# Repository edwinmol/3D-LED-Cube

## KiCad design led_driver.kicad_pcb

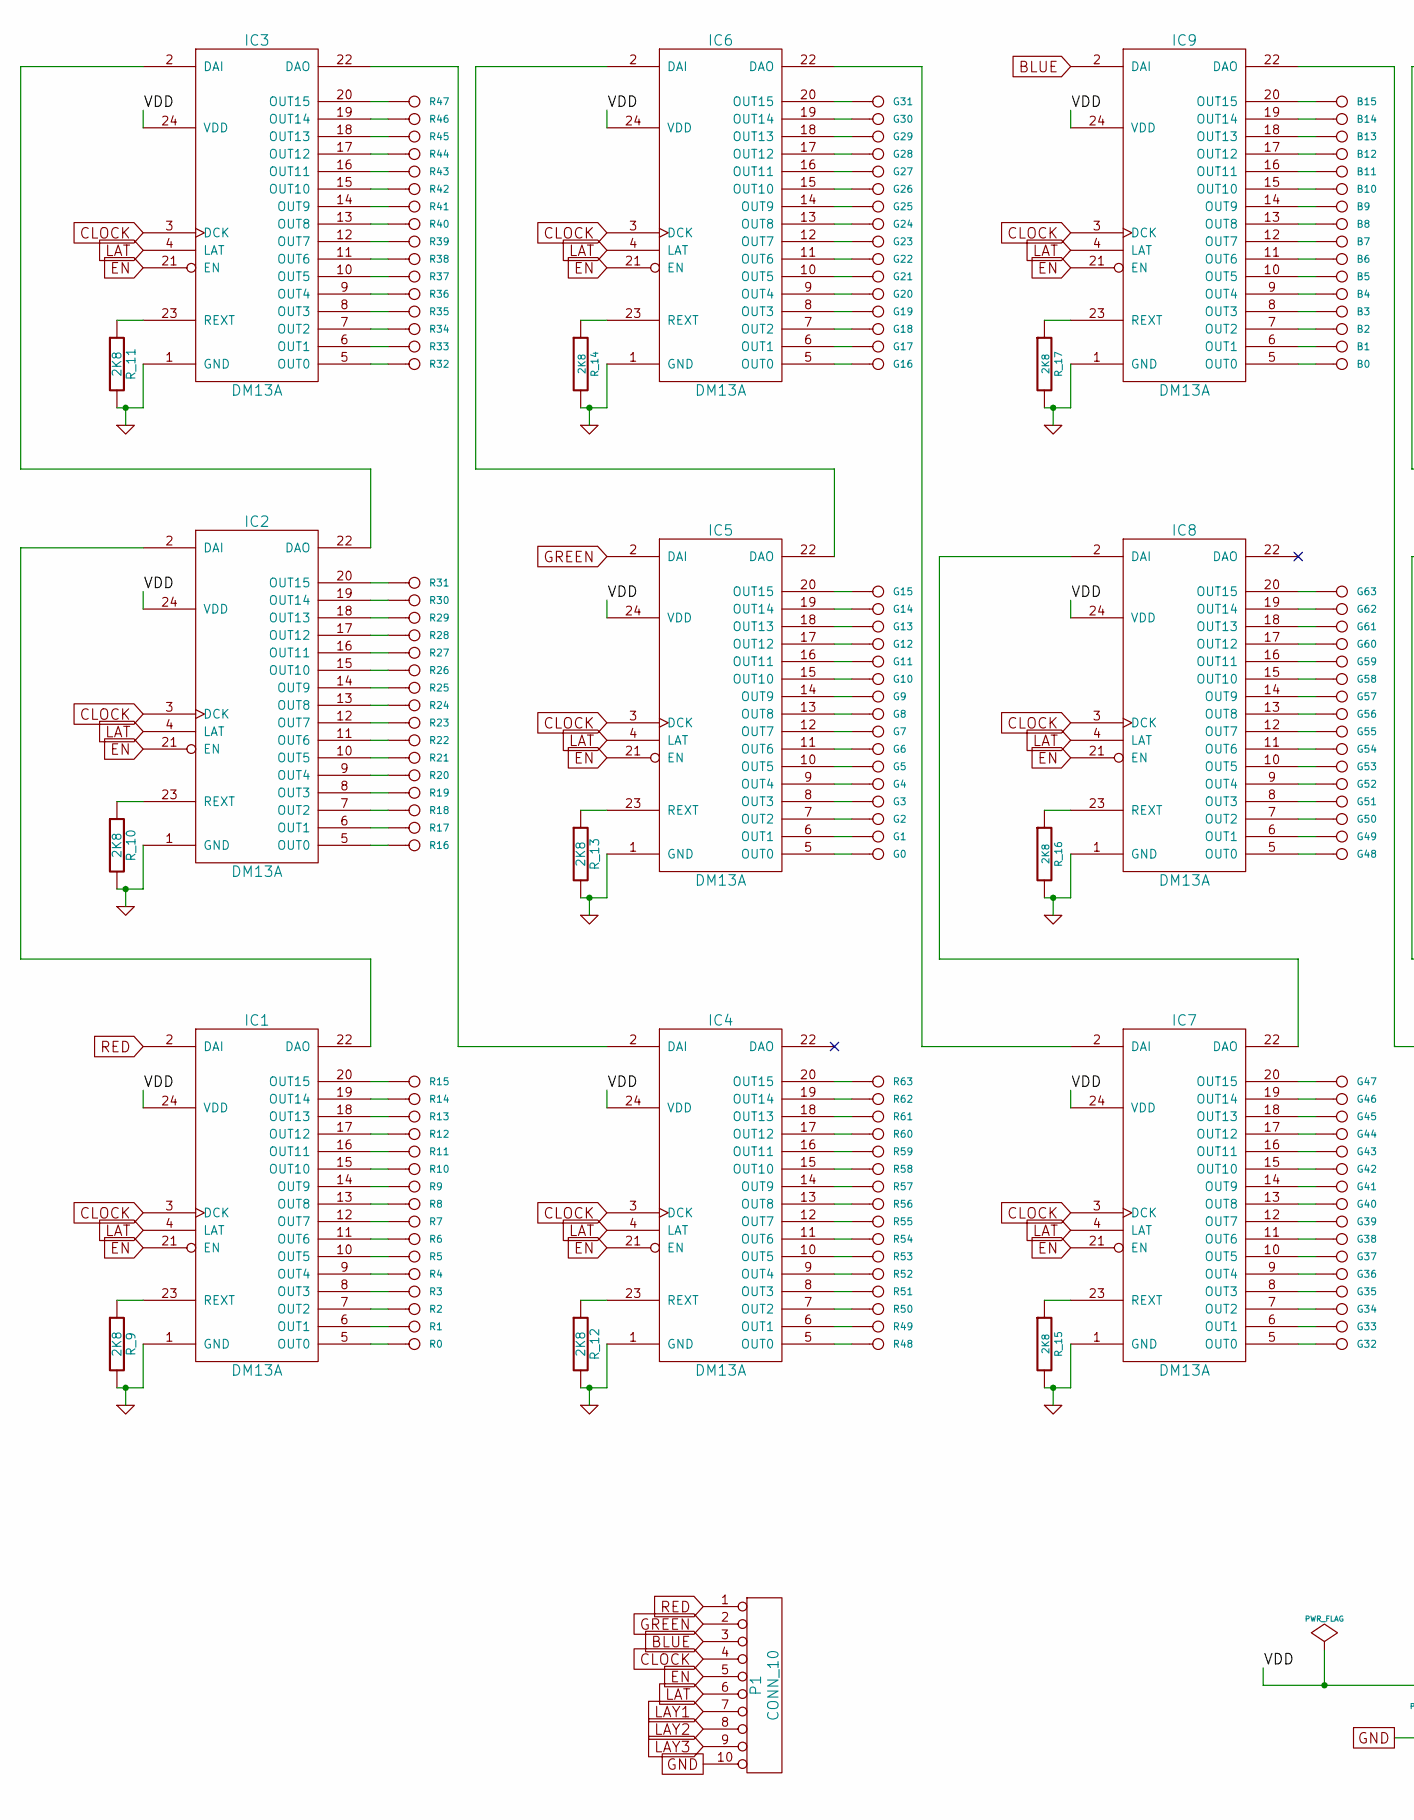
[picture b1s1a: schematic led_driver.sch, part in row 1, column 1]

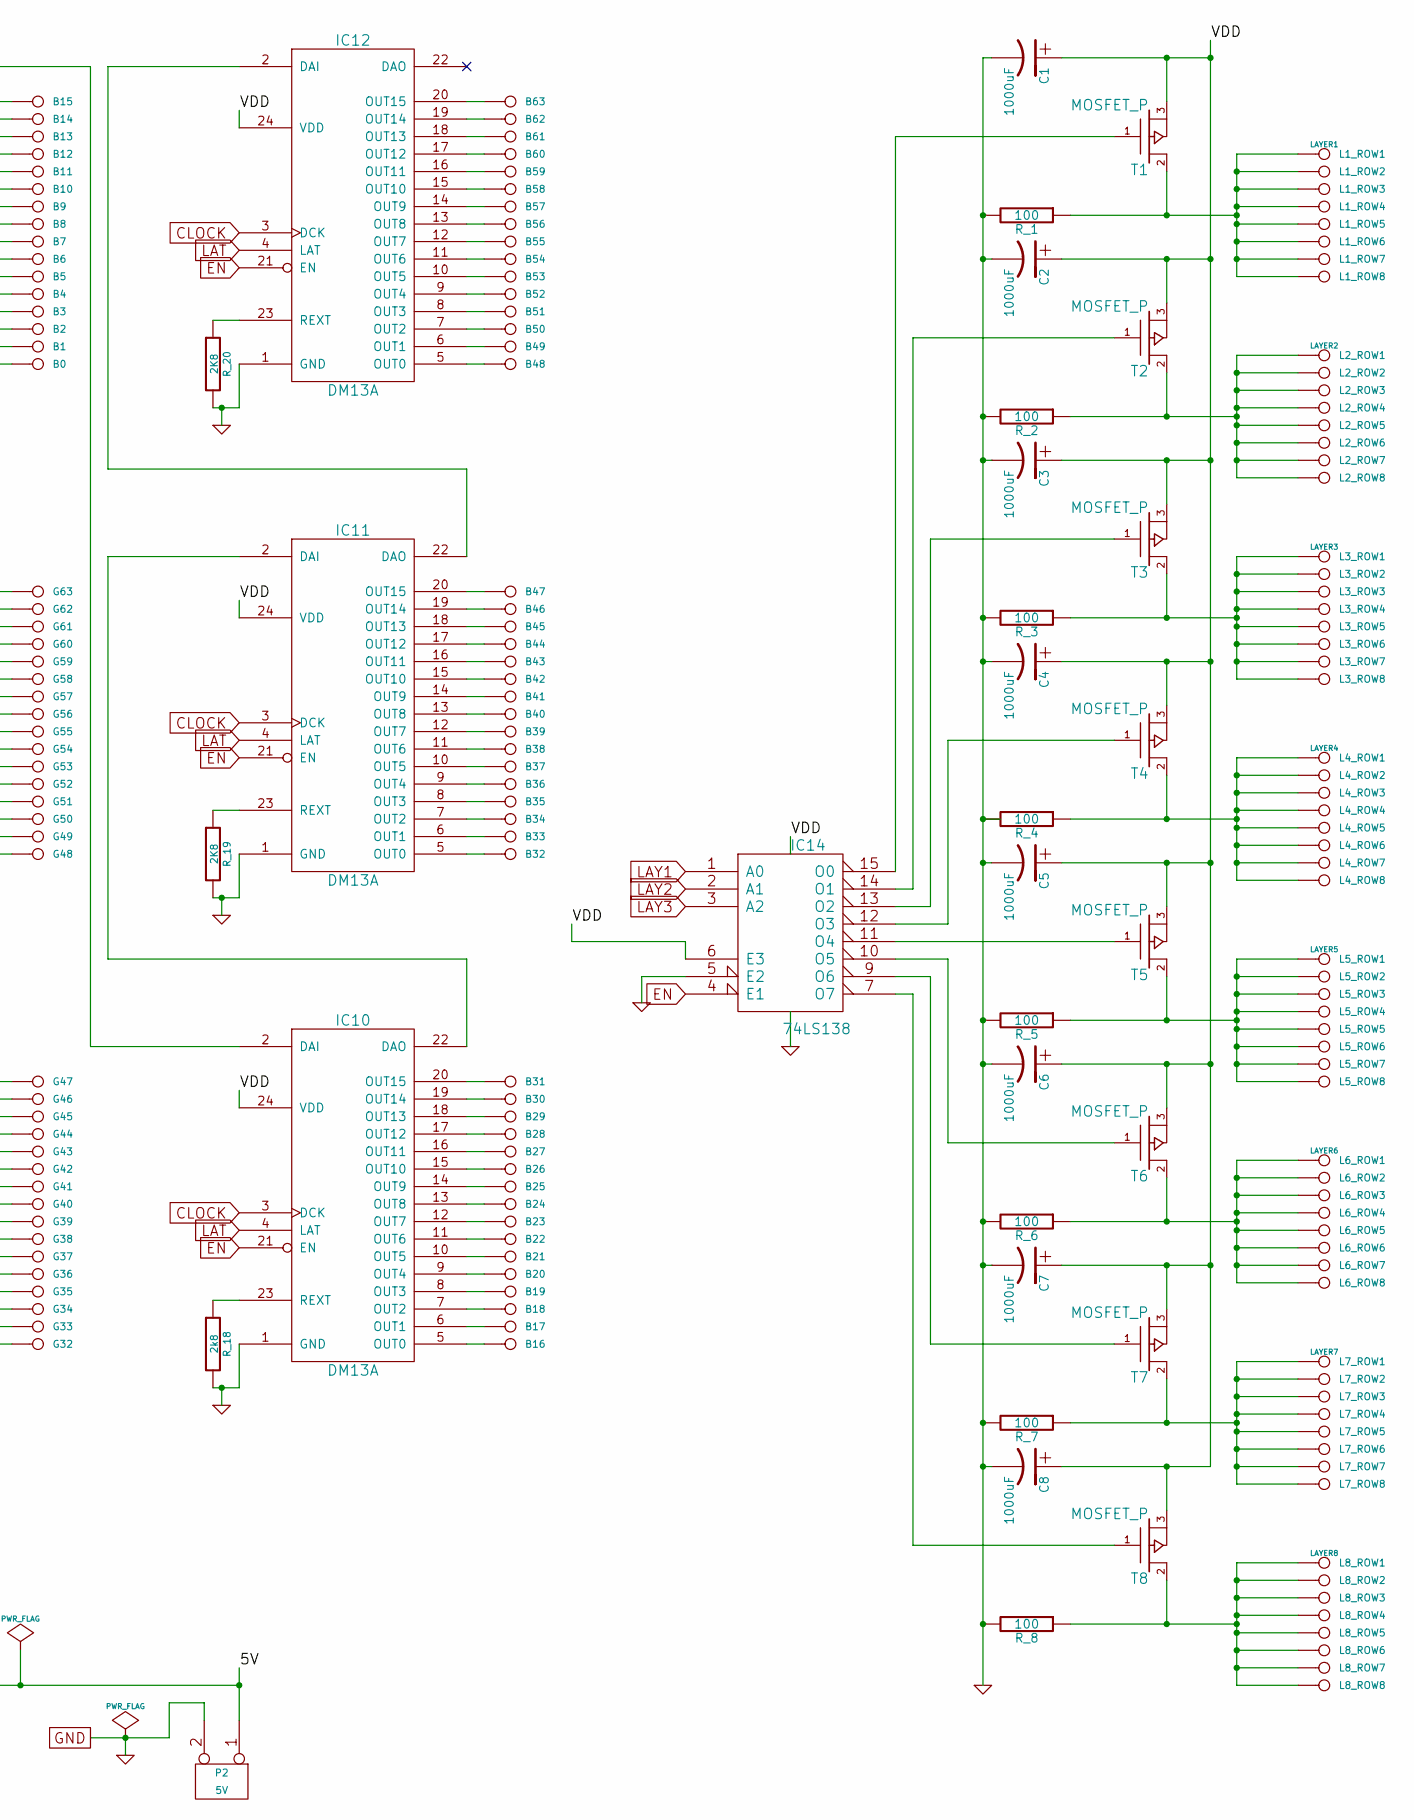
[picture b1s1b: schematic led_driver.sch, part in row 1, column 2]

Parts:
B0, B1, B2, B3, B4, B5, B6, B7, B8, B9, B10, B11, B12, B13, B14, B15, B16, B17, B18, B19, B20, B21, B22, B23, B24, B25, B26, B27, B28, B29, B30, B31, B32, B33, B34, B35, B36, B37, B38, B39, B40, B41, B42, B43, B44, B45, B46, B47, B48, B49, B50, B51, B52, B53, B54, B55, B56, B57, B58, B59, B60, B61, B62, B63: CONN_1
C1, C2, C3, C4, C5, C6, C7, C8: 1000uF
G0, G1, G2, G3, G4, G5, G6, G7, G8, G9, G10, G11, G12, G13, G14, G15, G16, G17, G18, G19, G20, G21, G22, G23, G24, G25, G26, G27, G28, G29, G30, G31, G32, G33, G34, G35, G36, G37, G38, G39, G40, G41, G42, G43, G44, G45, G46, G47, G48, G49, G50, G51, G52, G53, G54, G55, G56, G57, G58, G59, G60, G61, G62, G63: CONN_1
IC1, IC2, IC3, IC4, IC5, IC6, IC7, IC8, IC9, IC10, IC11, IC12: DM13A
IC14: 74LS138
L1_ROW1: LAYER1
L1_ROW2, L1_ROW3, L1_ROW4, L1_ROW5, L1_ROW6, L1_ROW7, L1_ROW8, L2_ROW2, L2_ROW3, L2_ROW4, L2_ROW5, L2_ROW6, L2_ROW7, L2_ROW8, L3_ROW2, L3_ROW3, L3_ROW4, L3_ROW5, L3_ROW6, L3_ROW7, L3_ROW8, L4_ROW2, L4_ROW3, L4_ROW4, L4_ROW5, L4_ROW6, L4_ROW7, L4_ROW8, L5_ROW2, L5_ROW3, L5_ROW4, L5_ROW5, L5_ROW6, L5_ROW7, L5_ROW8, L6_ROW2, L6_ROW3, L6_ROW4, L6_ROW5, L6_ROW6, L6_ROW7, L6_ROW8, L7_ROW2, L7_ROW3, L7_ROW4, L7_ROW5, L7_ROW6, L7_ROW7, L7_ROW8, L8_ROW2, L8_ROW3, L8_ROW4, L8_ROW5, L8_ROW6, L8_ROW7, L8_ROW8: CONN_1
L2_ROW1: LAYER2
L3_ROW1: LAYER3
L4_ROW1: LAYER4
L5_ROW1: LAYER5
L6_ROW1: LAYER6
L7_ROW1: LAYER7
L8_ROW1: LAYER8
P1: CONN_10
P2: 5V
R0, R1, R2, R3, R4, R5, R6, R7, R8, R9, R10, R11, R12, R13, R14, R15, R16, R17, R18, R19, R20, R21, R22, R23, R24, R25, R26, R27, R28, R29, R30, R31, R32, R33, R34, R35, R36, R37, R38, R39, R40, R41, R42, R43, R44, R45, R46, R47, R48, R49, R50, R51, R52, R53, R54, R55, R56, R57, R58, R59, R60, R61, R62, R63: CONN_1
R_1, R_2, R_3, R_4, R_5, R_6, R_7, R_8: 100
R_9, R_10, R_11, R_12, R_13: 2K8
R_14, R_15, R_16, R_17, R_19, R_20: 2K8
R_18: 2k8
T1, T2, T3, T4, T5, T6, T7, T8: MOSFET_P

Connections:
BLUE: IC9.2 (DAI), P1.3
CLOCK: IC1.3 (DCK), IC2.3 (DCK), IC3.3 (DCK), IC4.3 (DCK), IC5.3 (DCK), IC6.3 (DCK), IC7.3 (DCK), IC8.3 (DCK), IC9.3 (DCK), IC10.3 (DCK), IC11.3 (DCK), IC12.3 (DCK), P1.4
EN: IC1.21 (EN), IC2.21 (EN), IC3.21 (EN), IC4.21 (EN), IC5.21 (EN), IC6.21 (EN), IC7.21 (EN), IC8.21 (EN), IC9.21 (EN), IC10.21 (EN), IC11.21 (EN), IC12.21 (EN), IC14.4 (E1), P1.5
GND: C1.2, C2.2, C3.2, C4.2, C5.2, C6.2, C7.2, C8.2, IC1.1 (GND), IC2.1 (GND), IC3.1 (GND), IC4.1 (GND), IC5.1 (GND), IC6.1 (GND), IC7.1 (GND), IC8.1 (GND), IC9.1 (GND), IC10.1 (GND), IC11.1 (GND), IC12.1 (GND), IC14.5 (E2), IC14.8 (GND), P1.10, P2.2 (PM), R_1.2, R_2.2, R_3.2, R_4.2, R_5.2, R_6.2, R_7.2, R_8.2, R_9.2, R_10.2, R_11.2, R_12.2, R_13.2, R_14.2, R_15.2, R_16.2, R_17.2, R_18.2, R_19.2, R_20.2
GREEN: IC5.2 (DAI), P1.2
LAT: IC1.4 (LAT), IC2.4 (LAT), IC3.4 (LAT), IC4.4 (LAT), IC5.4 (LAT), IC6.4 (LAT), IC7.4 (LAT), IC8.4 (LAT), IC9.4 (LAT), IC10.4 (LAT), IC11.4 (LAT), IC12.4 (LAT), P1.6
LAY1: IC14.1 (A0), P1.7
LAY2: IC14.2 (A1), P1.8
LAY3: IC14.3 (A2), P1.9
unnamed: B0.1, IC9.5 (OUT0)
unnamed: B1.1, IC9.6 (OUT1)
unnamed: B2.1, IC9.7 (OUT2)
unnamed: B3.1, IC9.8 (OUT3)
unnamed: B4.1, IC9.9 (OUT4)
unnamed: B5.1, IC9.10 (OUT5)
unnamed: B6.1, IC9.11 (OUT6)
unnamed: B7.1, IC9.12 (OUT7)
unnamed: B8.1, IC9.13 (OUT8)
unnamed: B9.1, IC9.14 (OUT9)
unnamed: B10.1, IC9.15 (OUT10)
unnamed: B11.1, IC9.16 (OUT11)
unnamed: B12.1, IC9.17 (OUT12)
unnamed: B13.1, IC9.18 (OUT13)
unnamed: B14.1, IC9.19 (OUT14)
unnamed: B15.1, IC9.20 (OUT15)
unnamed: B16.1, IC10.5 (OUT0)
unnamed: B17.1, IC10.6 (OUT1)
unnamed: B18.1, IC10.7 (OUT2)
unnamed: B19.1, IC10.8 (OUT3)
unnamed: B20.1, IC10.9 (OUT4)
unnamed: B21.1, IC10.10 (OUT5)
unnamed: B22.1, IC10.11 (OUT6)
unnamed: B23.1, IC10.12 (OUT7)
unnamed: B24.1, IC10.13 (OUT8)
unnamed: B25.1, IC10.14 (OUT9)
unnamed: B26.1, IC10.15 (OUT10)
unnamed: B27.1, IC10.16 (OUT11)
unnamed: B28.1, IC10.17 (OUT12)
unnamed: B29.1, IC10.18 (OUT13)
unnamed: B30.1, IC10.19 (OUT14)
unnamed: B31.1, IC10.20 (OUT15)
unnamed: B32.1, IC11.5 (OUT0)
unnamed: B33.1, IC11.6 (OUT1)
unnamed: B34.1, IC11.7 (OUT2)
unnamed: B35.1, IC11.8 (OUT3)
unnamed: B36.1, IC11.9 (OUT4)
unnamed: B37.1, IC11.10 (OUT5)
unnamed: B38.1, IC11.11 (OUT6)
unnamed: B39.1, IC11.12 (OUT7)
unnamed: B40.1, IC11.13 (OUT8)
unnamed: B41.1, IC11.14 (OUT9)
unnamed: B42.1, IC11.15 (OUT10)
unnamed: B43.1, IC11.16 (OUT11)
unnamed: B44.1, IC11.17 (OUT12)
unnamed: B45.1, IC11.18 (OUT13)
unnamed: B46.1, IC11.19 (OUT14)
unnamed: B47.1, IC11.20 (OUT15)
unnamed: B48.1, IC12.5 (OUT0)
unnamed: B49.1, IC12.6 (OUT1)
unnamed: B50.1, IC12.7 (OUT2)
unnamed: B51.1, IC12.8 (OUT3)
unnamed: B52.1, IC12.9 (OUT4)
unnamed: B53.1, IC12.10 (OUT5)
unnamed: B54.1, IC12.11 (OUT6)
unnamed: B55.1, IC12.12 (OUT7)
unnamed: B56.1, IC12.13 (OUT8)
unnamed: B57.1, IC12.14 (OUT9)
unnamed: B58.1, IC12.15 (OUT10)
unnamed: B59.1, IC12.16 (OUT11)
unnamed: B60.1, IC12.17 (OUT12)
unnamed: B61.1, IC12.18 (OUT13)
unnamed: B62.1, IC12.19 (OUT14)
unnamed: B63.1, IC12.20 (OUT15)
unnamed: G0.1, IC5.5 (OUT0)
unnamed: G1.1, IC5.6 (OUT1)
unnamed: G2.1, IC5.7 (OUT2)
unnamed: G3.1, IC5.8 (OUT3)
unnamed: G4.1, IC5.9 (OUT4)
unnamed: G5.1, IC5.10 (OUT5)
unnamed: G6.1, IC5.11 (OUT6)
unnamed: G7.1, IC5.12 (OUT7)
unnamed: G8.1, IC5.13 (OUT8)
unnamed: G9.1, IC5.14 (OUT9)
unnamed: G10.1, IC5.15 (OUT10)
unnamed: G11.1, IC5.16 (OUT11)
unnamed: G12.1, IC5.17 (OUT12)
unnamed: G13.1, IC5.18 (OUT13)
unnamed: G14.1, IC5.19 (OUT14)
unnamed: G15.1, IC5.20 (OUT15)
unnamed: G16.1, IC6.5 (OUT0)
unnamed: G17.1, IC6.6 (OUT1)
unnamed: G18.1, IC6.7 (OUT2)
unnamed: G19.1, IC6.8 (OUT3)
unnamed: G20.1, IC6.9 (OUT4)
unnamed: G21.1, IC6.10 (OUT5)
unnamed: G22.1, IC6.11 (OUT6)
unnamed: G23.1, IC6.12 (OUT7)
unnamed: G24.1, IC6.13 (OUT8)
unnamed: G25.1, IC6.14 (OUT9)
unnamed: G26.1, IC6.15 (OUT10)
unnamed: G27.1, IC6.16 (OUT11)
unnamed: G28.1, IC6.17 (OUT12)
unnamed: G29.1, IC6.18 (OUT13)
unnamed: G30.1, IC6.19 (OUT14)
unnamed: G31.1, IC6.20 (OUT15)
unnamed: G32.1, IC7.5 (OUT0)
unnamed: G33.1, IC7.6 (OUT1)
unnamed: G34.1, IC7.7 (OUT2)
unnamed: G35.1, IC7.8 (OUT3)
unnamed: G36.1, IC7.9 (OUT4)
unnamed: G37.1, IC7.10 (OUT5)
unnamed: G38.1, IC7.11 (OUT6)
unnamed: G39.1, IC7.12 (OUT7)
unnamed: G40.1, IC7.13 (OUT8)
unnamed: G41.1, IC7.14 (OUT9)
unnamed: G42.1, IC7.15 (OUT10)
unnamed: G43.1, IC7.16 (OUT11)
unnamed: G44.1, IC7.17 (OUT12)
unnamed: G45.1, IC7.18 (OUT13)
unnamed: G46.1, IC7.19 (OUT14)
unnamed: G47.1, IC7.20 (OUT15)
unnamed: G48.1, IC8.5 (OUT0)
unnamed: G49.1, IC8.6 (OUT1)
unnamed: G50.1, IC8.7 (OUT2)
unnamed: G51.1, IC8.8 (OUT3)
unnamed: G52.1, IC8.9 (OUT4)
unnamed: G53.1, IC8.10 (OUT5)
unnamed: G54.1, IC8.11 (OUT6)
unnamed: G55.1, IC8.12 (OUT7)
unnamed: G56.1, IC8.13 (OUT8)
unnamed: G57.1, IC8.14 (OUT9)
unnamed: G58.1, IC8.15 (OUT10)
unnamed: G59.1, IC8.16 (OUT11)
unnamed: G60.1, IC8.17 (OUT12)
unnamed: G61.1, IC8.18 (OUT13)
unnamed: G62.1, IC8.19 (OUT14)
unnamed: G63.1, IC8.20 (OUT15)
unnamed: IC1.5 (OUT0), R0.1
unnamed: IC1.6 (OUT1), R1.1
unnamed: IC1.7 (OUT2), R2.1
unnamed: IC1.8 (OUT3), R3.1
unnamed: IC1.9 (OUT4), R4.1
unnamed: IC1.10 (OUT5), R5.1
unnamed: IC1.11 (OUT6), R6.1
unnamed: IC1.12 (OUT7), R7.1
unnamed: IC1.13 (OUT8), R8.1
unnamed: IC1.14 (OUT9), R9.1
unnamed: IC1.15 (OUT10), R10.1
unnamed: IC1.16 (OUT11), R11.1
unnamed: IC1.17 (OUT12), R12.1
unnamed: IC1.18 (OUT13), R13.1
unnamed: IC1.19 (OUT14), R14.1
unnamed: IC1.20 (OUT15), R15.1
unnamed: IC1.22 (DAO), IC2.2 (DAI)
unnamed: IC1.23 (REXT), R_9.1
unnamed: IC2.5 (OUT0), R16.1
unnamed: IC2.6 (OUT1), R17.1
unnamed: IC2.7 (OUT2), R18.1
unnamed: IC2.8 (OUT3), R19.1
unnamed: IC2.9 (OUT4), R20.1
unnamed: IC2.10 (OUT5), R21.1
unnamed: IC2.11 (OUT6), R22.1
unnamed: IC2.12 (OUT7), R23.1
unnamed: IC2.13 (OUT8), R24.1
unnamed: IC2.14 (OUT9), R25.1
unnamed: IC2.15 (OUT10), R26.1
unnamed: IC2.16 (OUT11), R27.1
unnamed: IC2.17 (OUT12), R28.1
unnamed: IC2.18 (OUT13), R29.1
unnamed: IC2.19 (OUT14), R30.1
unnamed: IC2.20 (OUT15), R31.1
unnamed: IC2.22 (DAO), IC3.2 (DAI)
unnamed: IC2.23 (REXT), R_10.1
unnamed: IC3.5 (OUT0), R32.1
unnamed: IC3.6 (OUT1), R33.1
unnamed: IC3.7 (OUT2), R34.1
unnamed: IC3.8 (OUT3), R35.1
unnamed: IC3.9 (OUT4), R36.1
unnamed: IC3.10 (OUT5), R37.1
unnamed: IC3.11 (OUT6), R38.1
unnamed: IC3.12 (OUT7), R39.1
unnamed: IC3.13 (OUT8), R40.1
unnamed: IC3.14 (OUT9), R41.1
unnamed: IC3.15 (OUT10), R42.1
unnamed: IC3.16 (OUT11), R43.1
unnamed: IC3.17 (OUT12), R44.1
unnamed: IC3.18 (OUT13), R45.1
unnamed: IC3.19 (OUT14), R46.1
unnamed: IC3.20 (OUT15), R47.1
unnamed: IC3.22 (DAO), IC4.2 (DAI)
unnamed: IC3.23 (REXT), R_11.1
unnamed: IC4.5 (OUT0), R48.1
unnamed: IC4.6 (OUT1), R49.1
unnamed: IC4.7 (OUT2), R50.1
unnamed: IC4.8 (OUT3), R51.1
unnamed: IC4.9 (OUT4), R52.1
unnamed: IC4.10 (OUT5), R53.1
unnamed: IC4.11 (OUT6), R54.1
unnamed: IC4.12 (OUT7), R55.1
unnamed: IC4.13 (OUT8), R56.1
unnamed: IC4.14 (OUT9), R57.1
unnamed: IC4.15 (OUT10), R58.1
unnamed: IC4.16 (OUT11), R59.1
unnamed: IC4.17 (OUT12), R60.1
unnamed: IC4.18 (OUT13), R61.1
unnamed: IC4.19 (OUT14), R62.1
unnamed: IC4.20 (OUT15), R63.1
unnamed: IC4.23 (REXT), R_12.1
unnamed: IC5.22 (DAO), IC6.2 (DAI)
unnamed: IC5.23 (REXT), R_13.1
unnamed: IC6.22 (DAO), IC7.2 (DAI)
unnamed: IC6.23 (REXT), R_14.1
unnamed: IC7.22 (DAO), IC8.2 (DAI)
unnamed: IC7.23 (REXT), R_15.1
unnamed: IC8.23 (REXT), R_16.1
unnamed: IC9.23 (REXT), R_17.1
unnamed: IC9.22 (DAO), IC10.2 (DAI)
unnamed: IC10.22 (DAO), IC11.2 (DAI)
unnamed: IC10.23 (REXT), R_18.1
unnamed: IC11.22 (DAO), IC12.2 (DAI)
unnamed: IC11.23 (REXT), R_19.1
unnamed: IC12.23 (REXT), R_20.1
unnamed: IC14.7 (O7), T8.1 (G)
unnamed: IC14.9 (O6), T7.1 (G)
unnamed: IC14.10 (O5), T6.1 (G)
unnamed: IC14.11 (O4), T5.1 (G)
unnamed: IC14.12 (O3), T4.1 (G)
unnamed: IC14.13 (O2), T3.1 (G)
unnamed: IC14.14 (O1), T2.1 (G)
unnamed: IC14.15 (O0), T1.1 (G)
unnamed: L1_ROW1.1, L1_ROW2.1, L1_ROW3.1, L1_ROW4.1, L1_ROW5.1, L1_ROW6.1, L1_ROW7.1, L1_ROW8.1, R_1.1, T1.2 (D)
unnamed: L2_ROW1.1, L2_ROW2.1, L2_ROW3.1, L2_ROW4.1, L2_ROW5.1, L2_ROW6.1, L2_ROW7.1, L2_ROW8.1, R_2.1, T2.2 (D)
unnamed: L3_ROW1.1, L3_ROW2.1, L3_ROW3.1, L3_ROW4.1, L3_ROW5.1, L3_ROW6.1, L3_ROW7.1, L3_ROW8.1, R_3.1, T3.2 (D)
unnamed: L4_ROW1.1, L4_ROW2.1, L4_ROW3.1, L4_ROW4.1, L4_ROW5.1, L4_ROW6.1, L4_ROW7.1, L4_ROW8.1, R_4.1, T4.2 (D)
unnamed: L5_ROW1.1, L5_ROW2.1, L5_ROW3.1, L5_ROW4.1, L5_ROW5.1, L5_ROW6.1, L5_ROW7.1, L5_ROW8.1, R_5.1, T5.2 (D)
unnamed: L6_ROW1.1, L6_ROW2.1, L6_ROW3.1, L6_ROW4.1, L6_ROW5.1, L6_ROW6.1, L6_ROW7.1, L6_ROW8.1, R_6.1, T6.2 (D)
unnamed: L7_ROW1.1, L7_ROW2.1, L7_ROW3.1, L7_ROW4.1, L7_ROW5.1, L7_ROW6.1, L7_ROW7.1, L7_ROW8.1, R_7.1, T7.2 (D)
unnamed: L8_ROW1.1, L8_ROW2.1, L8_ROW3.1, L8_ROW4.1, L8_ROW5.1, L8_ROW6.1, L8_ROW7.1, L8_ROW8.1, R_8.1, T8.2 (D)
RED: IC1.2 (DAI), P1.1
VCC: C1.1, C2.1, C3.1, C4.1, C5.1, C6.1, C7.1, C8.1, IC1.24 (VDD), IC2.24 (VDD), IC3.24 (VDD), IC4.24 (VDD), IC5.24 (VDD), IC6.24 (VDD), IC7.24 (VDD), IC8.24 (VDD), IC9.24 (VDD), IC10.24 (VDD), IC11.24 (VDD), IC12.24 (VDD), IC14.6 (E3), IC14.16 (VCC), P2.1, T1.3 (S), T2.3 (S), T3.3 (S), T4.3 (S), T5.3 (S), T6.3 (S), T7.3 (S), T8.3 (S)

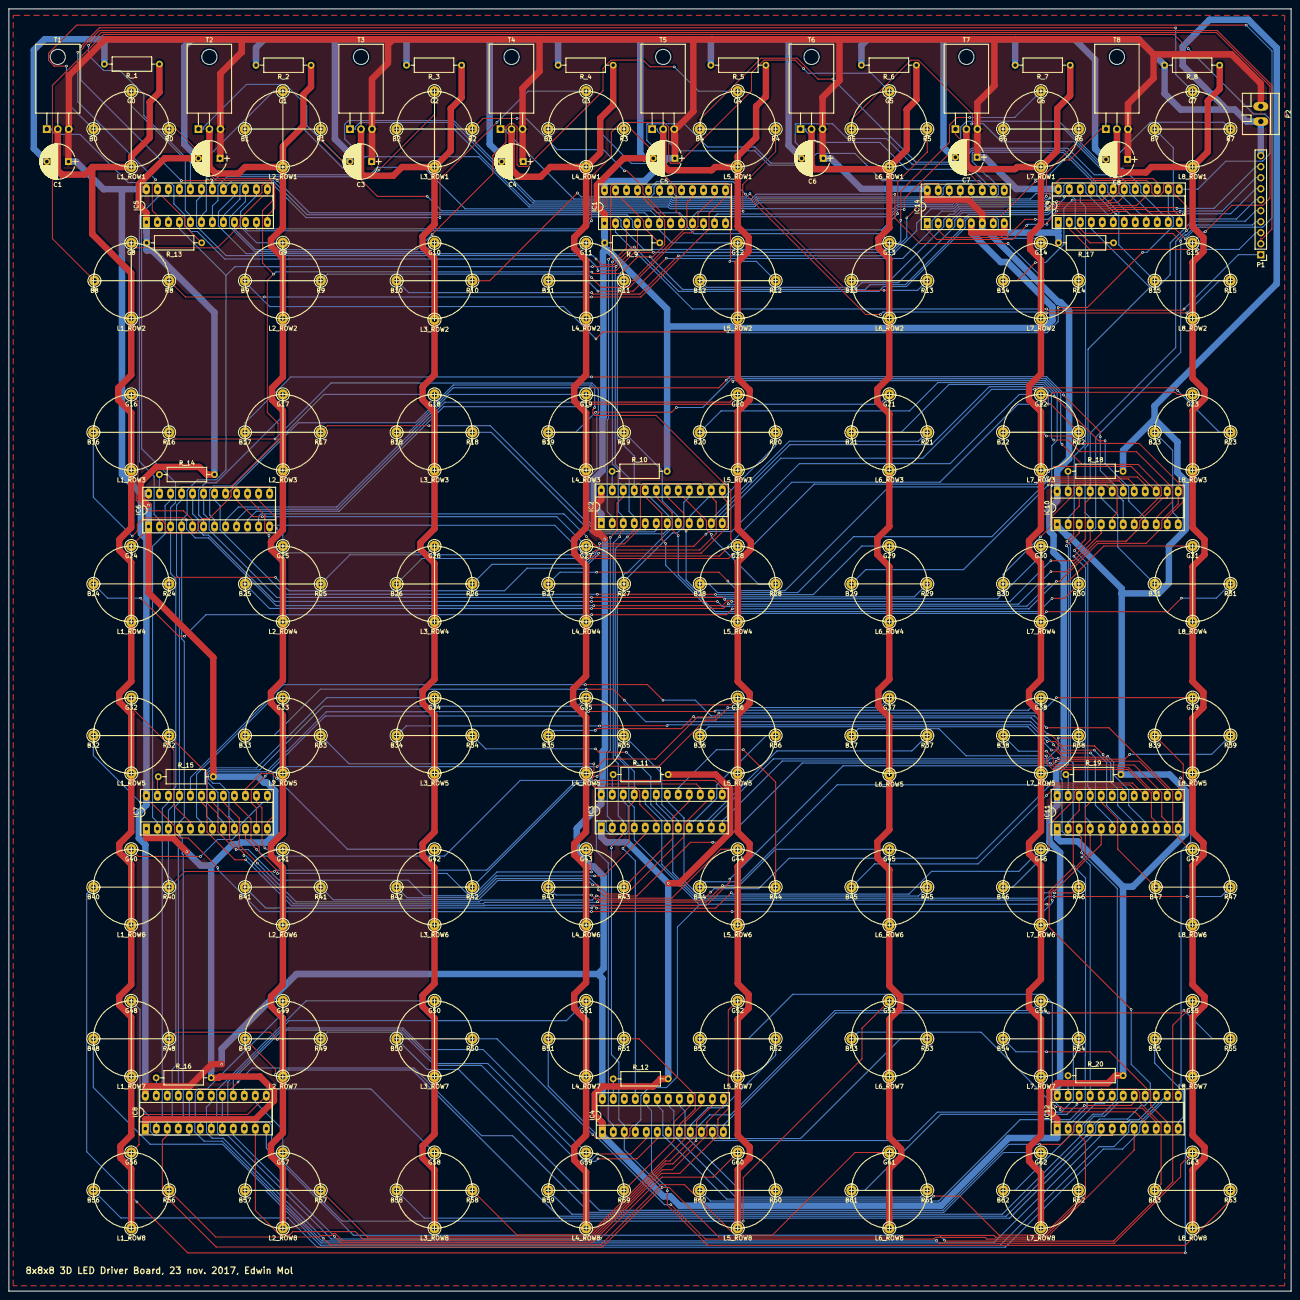
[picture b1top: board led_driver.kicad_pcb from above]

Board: 2 copper layers, 296.0 x 296.0 mm, 307 parts (0 on the bottom side), 240 nets.

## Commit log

2017-11-22 finished manual routing
2017-11-23 finished pcb
2017-11-24 version 1.0
